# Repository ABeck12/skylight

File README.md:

# Changes to be made for v2:
## For Sure:
- Move RESET and POWER buttons closer to pcb edge
- Change batter connection to be vertical instead of right angle connector
- Move reset trace such that it is not about battery trace

## Potential:
- Switch to surface mount diodes?
- Add LEDs for backlight?
- Move thumb cluster keys to be at a lesser angle?

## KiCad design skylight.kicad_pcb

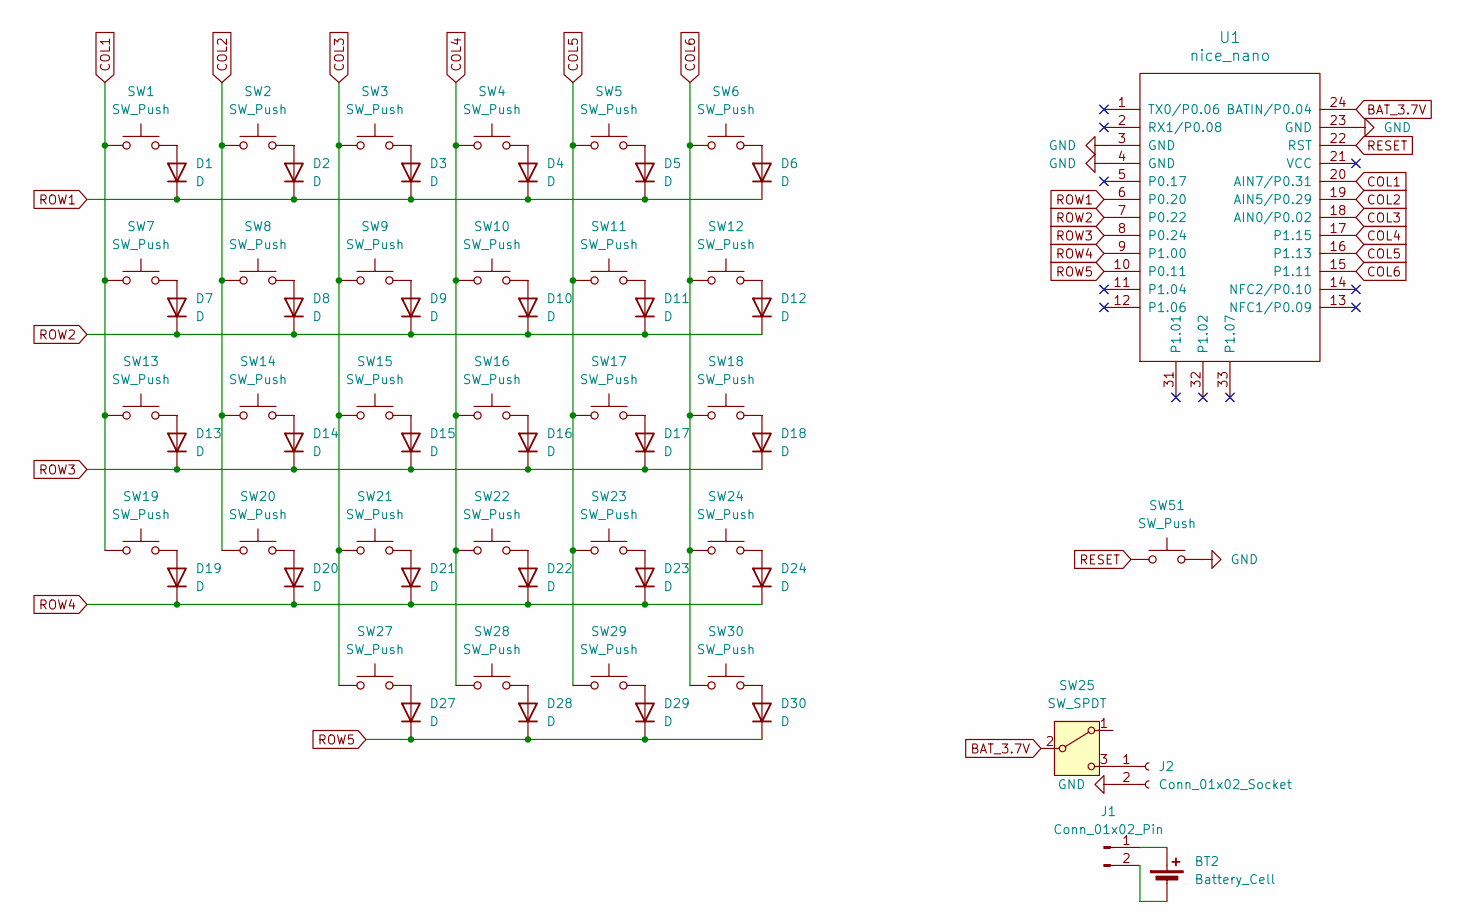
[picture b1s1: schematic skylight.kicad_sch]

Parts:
BT2: Battery_Cell
D1, D2, D3, D4, D5, D6, D7, D8, D9, D10, D11, D12, D13, D14, D15, D16, D17, D18, D19, D20, D21, D22, D23, D24, D27, D28, D29, D30: D; D_DO-35_SOD27_P7.62mm_Horizontal
J1: Conn_01x02_Pin
J2: Conn_01x02_Socket; JST_PH_S2B-PH-K_1x02_P2.00mm_Horizontal
SW1, SW7, SW13, SW19, SW29, SW30: SW_Push; Kailh_socket_PG1350_reversible_1.5u
SW2, SW3, SW4, SW5, SW6, SW8, SW9, SW10, SW11, SW12, SW14, SW15, SW16, SW17, SW18, SW20, SW21, SW22, SW23, SW24, SW27, SW28: SW_Push; Kailh_socket_PG1350_reversible_1u
SW25: SW_SPDT; SSSS810701
SW51: SW_Push; Panasonic_EVQPUJ_EVQPUA
U1: nice_nano; nice_nano_reverseible

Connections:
BAT_3.7V: SW25.2 (B), U1.24 (BATIN/P0.04); also elsewhere on the board
COL1: SW1.1, SW7.1, SW13.1, SW19.1, U1.20 (AIN7/P0.31)
COL2: SW2.1, SW8.1, SW14.1, SW20.1, U1.19 (AIN5/P0.29)
COL3: SW3.1, SW9.1, SW15.1, SW21.1, SW27.1, U1.18 (AIN0/P0.02)
COL4: SW4.1, SW10.1, SW16.1, SW22.1, SW28.1, U1.17 (P1.15)
COL5: SW5.1, SW11.1, SW17.1, SW23.1, SW29.1, U1.16 (P1.13)
COL6: SW6.1, SW12.1, SW18.1, SW24.1, SW30.1, U1.15 (P1.11)
GND: J2.2, SW51.2, U1.3 (GND), U1.4 (GND), U1.23 (GND); also elsewhere on the board
unnamed: BT2.1 (+), J1.1
unnamed: BT2.2 (-), J1.2
unnamed: D1.2 (A), SW1.2
unnamed: D2.2 (A), SW2.2
unnamed: D3.2 (A), SW3.2
unnamed: D4.2 (A), SW4.2
unnamed: D5.2 (A), SW5.2
unnamed: D6.2 (A), SW6.2
unnamed: D7.2 (A), SW7.2
unnamed: D8.2 (A), SW8.2
unnamed: D9.2 (A), SW9.2
unnamed: D10.2 (A), SW10.2
unnamed: D11.2 (A), SW11.2
unnamed: D12.2 (A), SW12.2
unnamed: D13.2 (A), SW13.2
unnamed: D14.2 (A), SW14.2
unnamed: D15.2 (A), SW15.2
unnamed: D16.2 (A), SW16.2
unnamed: D17.2 (A), SW17.2
unnamed: D18.2 (A), SW18.2
unnamed: D19.2 (A), SW19.2
unnamed: D20.2 (A), SW20.2
unnamed: D21.2 (A), SW21.2
unnamed: D22.2 (A), SW22.2
unnamed: D23.2 (A), SW23.2
unnamed: D24.2 (A), SW24.2
unnamed: D27.2 (A), SW27.2
unnamed: D28.2 (A), SW28.2
unnamed: D29.2 (A), SW29.2
unnamed: D30.2 (A), SW30.2
unnamed 38: J2.1, SW25.3 (C); also elsewhere on the board
RESET: SW51.1, U1.22 (RST); also elsewhere on the board
ROW1: D1.1 (K), D2.1 (K), D3.1 (K), D4.1 (K), D5.1 (K), D6.1 (K), U1.6 (P0.20)
ROW2: D7.1 (K), D8.1 (K), D9.1 (K), D10.1 (K), D11.1 (K), D12.1 (K), U1.7 (P0.22)
ROW3: D13.1 (K), D14.1 (K), D15.1 (K), D16.1 (K), D17.1 (K), D18.1 (K), U1.8 (P0.24)
ROW4: D19.1 (K), D20.1 (K), D21.1 (K), D22.1 (K), D23.1 (K), D24.1 (K), U1.9 (P1.00)
ROW5: D27.1 (K), D28.1 (K), D29.1 (K), D30.1 (K), U1.10 (P0.11)

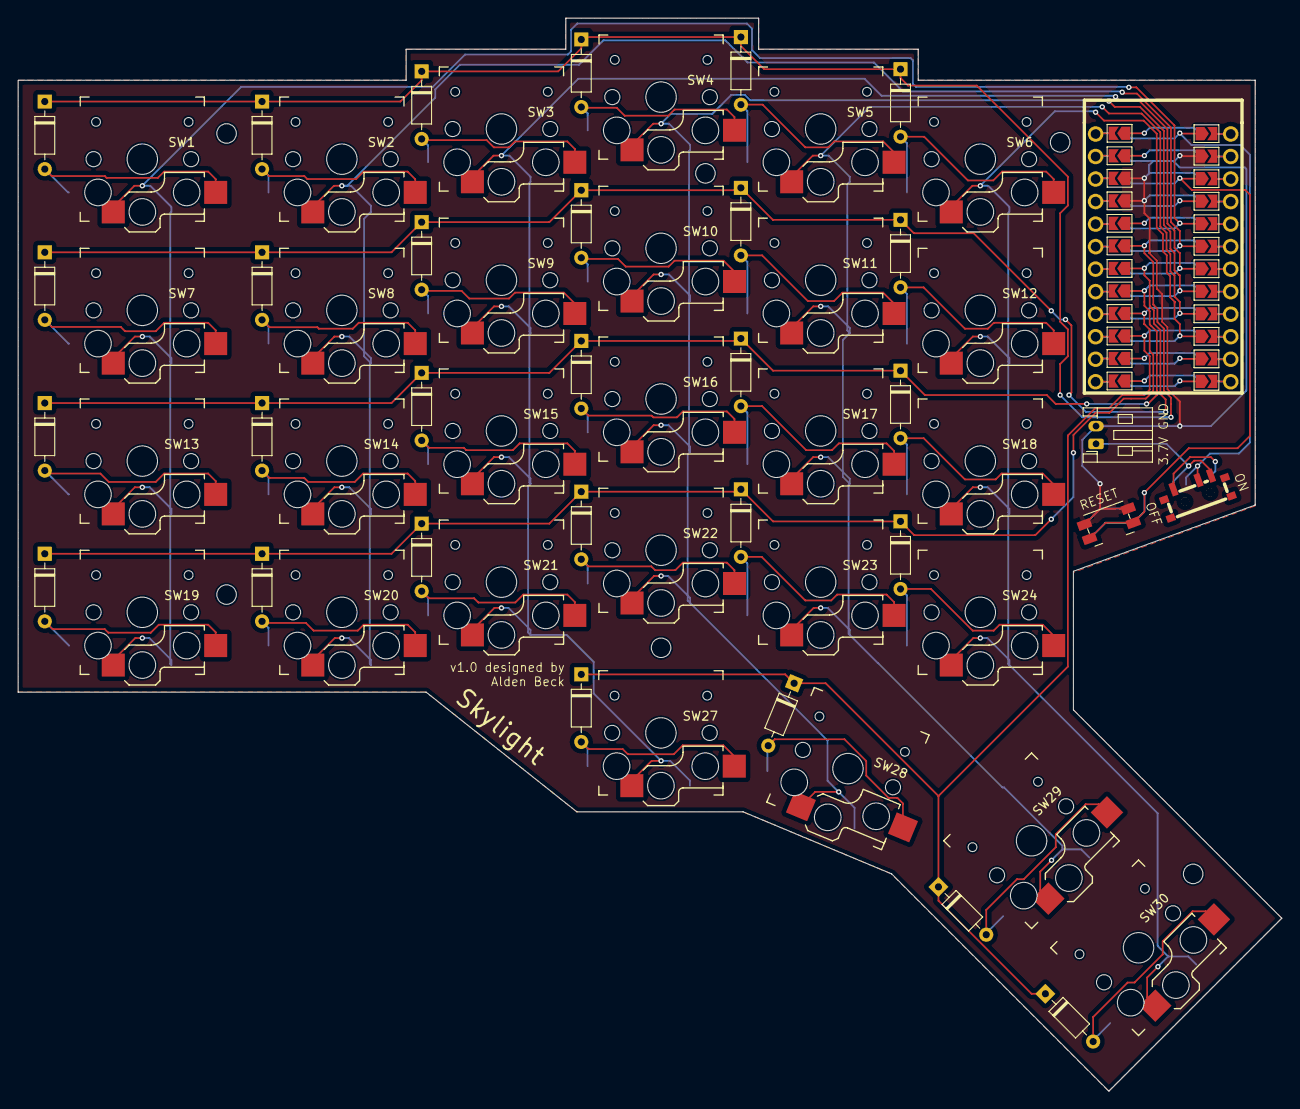
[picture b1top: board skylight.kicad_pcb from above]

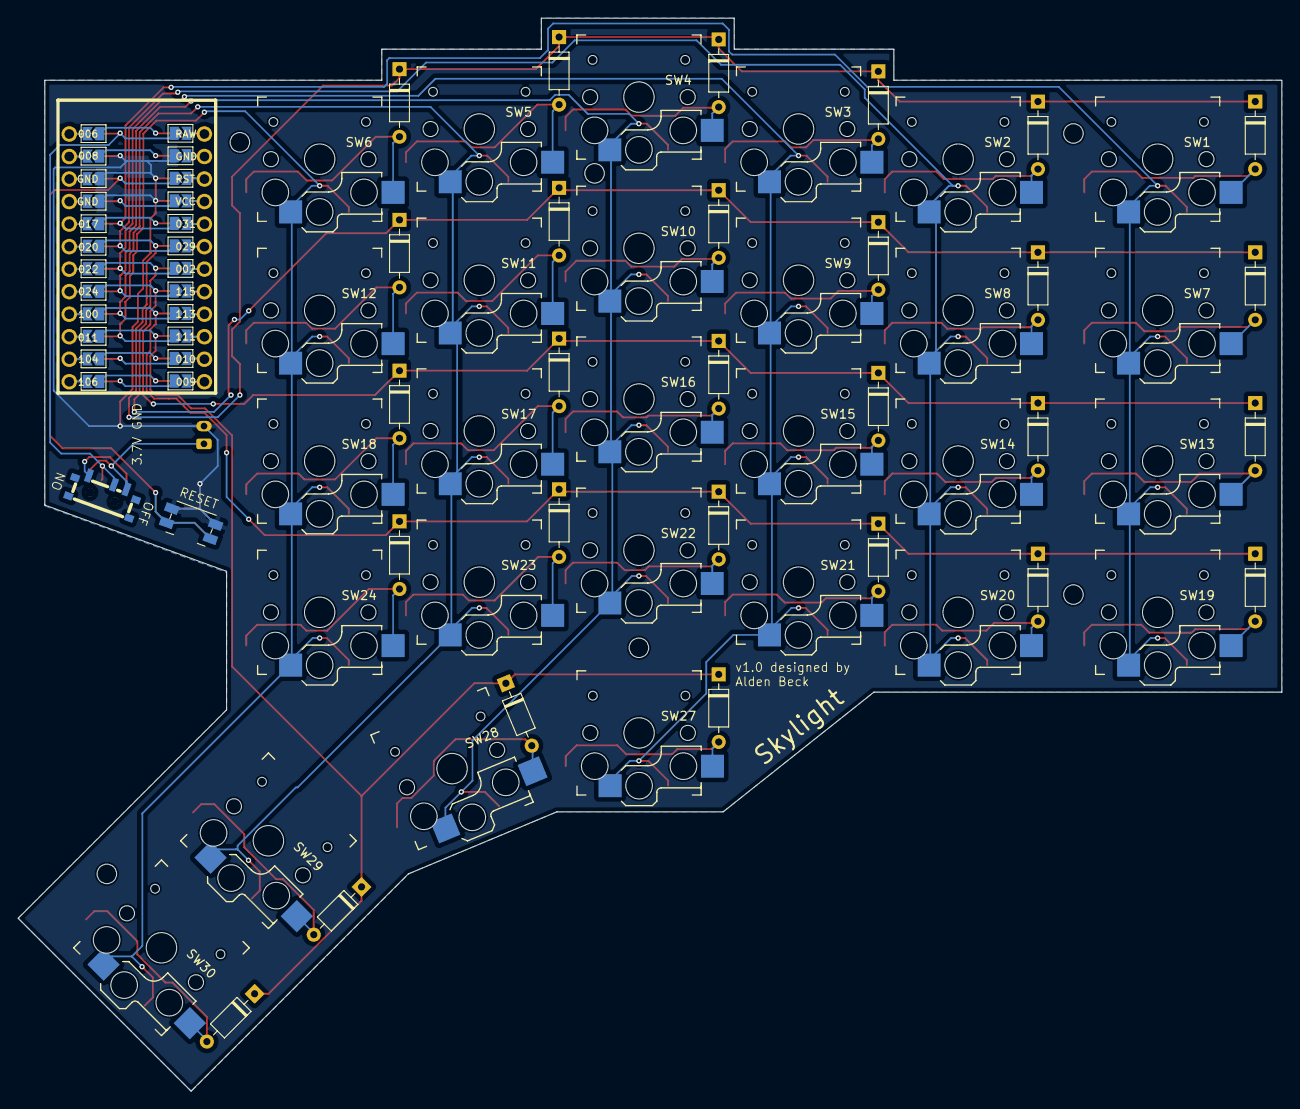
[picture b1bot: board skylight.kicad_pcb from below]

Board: 2 copper layers, 142.5 x 121.0 mm, 62 parts (2 on the bottom side), 43 nets.

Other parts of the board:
SW25#2: SW_SPDT; SSSS810701
SW51#2: SW_Push; Panasonic_EVQPUJ_EVQPUA

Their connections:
BAT_3.7V: SW25#2.2 (B); also elsewhere on the board
GND: SW51#2.2; also elsewhere on the board
unnamed 38: SW25#2.3 (C); also elsewhere on the board
RESET: SW51#2.1; also elsewhere on the board

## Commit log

2025-03-18 init
2025-04-05 Added changes for potential v2 inside README
2025-04-27 Added case
2025-04-27 Moved pcb stuff to new folder
